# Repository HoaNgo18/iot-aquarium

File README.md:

# IoT Aquarium

Hệ thống theo dõi nhiệt độ, pH và độ đục tương đối của nước trong bể cá. ESP32 gửi dữ liệu qua MQTT về server; giao diện web hiển thị số đo, lịch sử và cảnh báo khi vượt ngưỡng cấu hình.

## Chức năng

- Theo dõi số đo và trạng thái kết nối của thiết bị.
- Xem biểu đồ lịch sử theo từng chỉ số.
- Cấu hình ngưỡng và xác nhận cảnh báo.
- Giả lập dữ liệu để thử hệ thống khi chưa kết nối cảm biến.

## Công nghệ

- **Thiết bị:** ESP32, DS18B20, PH-4502C, cảm biến độ đục MJKDZ.
- **Backend:** Python, FastAPI, PostgreSQL, Mosquitto MQTT.
- **Frontend:** Vue 3, TypeScript, Vite; cập nhật dữ liệu qua WebSocket.
- **Triển khai:** Docker Compose; firmware quản lý bằng PlatformIO.

## Chạy local

Cần Docker Compose. Tạo `.env` từ `.env.example` nếu chưa có, điều chỉnh cấu hình rồi khởi động:

```powershell
if (-not (Test-Path .env)) { Copy-Item .env.example .env }
docker compose up -d --build
```

- Giao diện: http://localhost:5173
- API: http://localhost:8000/docs

## Cấu trúc thư mục

```text
backend/         FastAPI: api -> services/domain -> repositories, migration Alembic
firmware/        ESP32 (PlatformIO), test host, sketch chẩn đoán
frontend/        Dashboard Vue; tests/ là unit test, tests/browser/ là kịch bản Playwright
simulator/       Bộ phát telemetry giả lập qua MQTT
infrastructure/  Cấu hình Mosquitto
scripts/         Smoke test toàn hệ thống; uart/ là công cụ thu và phân tích log Serial
```

## Tài liệu

- [Cấu hình và nạp firmware](firmware/README.md)
- [Chạy dữ liệu giả lập](simulator/README.md)

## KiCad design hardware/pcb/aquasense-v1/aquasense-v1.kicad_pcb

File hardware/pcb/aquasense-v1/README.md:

# AquaSense v1.0 — mạch đế ESP32

Mạch hai lớp **80 × 60 mm**, FR-4 1,6 mm, đồng 1 oz. Cắm ESP32 DevKit 30 chân qua hai header cái 1×15; bốn đầu cảm biến dùng ổ khóa JST-XH để cắm/rút gọn gàng. Không phải mạch ESP32 rời và không thay thế module PH-4502C/MJKDZ.

**Trạng thái:** đã đi dây; KiCad 9.0.2 chạy trong Docker. ERC: 0 lỗi/0 cảnh báo. DRC kèm đối chiếu schematic: 0 vi phạm, 0 kết nối hở, 0 sai khác footprint/net. Chưa sản xuất hay thử điện trên PCB thật.

## Mở và xem

Mở `aquasense-v1.kicad_pro` bằng KiCad 9 trở lên. File sử dụng định dạng KiCad 9, thuộc yêu cầu “KiCad 8 trở lên”. Cần cài bộ thư viện symbol/footprint chuẩn KiCad. Thư viện riêng `aquasense.kicad_sym`, `aquasense.pretty/` được khai báo qua hai bảng thư viện trong project.

- `preview/top-3d.png`, `bottom-3d.png`: ảnh bo trần, chưa lắp linh kiện; máy dựng ảnh không cài gói mô hình 3D linh kiện.
- `preview/pcb-top.svg`: đường đồng và lụa mặt trên.
- `preview/print-1to1.pdf`: mặt trên khổ A4 tỉ lệ 1:1, kèm thước chuẩn 50 mm; khi in phải chọn 100%/Actual size.
- `preview/schematic.pdf`, `schematic.png`, `aquasense-v1.svg`: sơ đồ nguyên lý.
- `reports/erc.rpt`, `drc.rpt`: báo cáo KiCad cuối cùng, không có mục loại trừ lỗi.
- `reports/design-audit.json`: toàn bộ gán net, thứ tự chân JST-XH, ba GPIO, khoảng cách socket và vùng anten đã được kiểm tra.
- `bom.csv`: một hàng cho mỗi reference. U1 tính **1 bộ gồm 2 socket cái 1×15**, không phải hai board ESP32.
- `fab/aquasense-v1-gerber.zip`: Gerber, PTH/NPTH Excellon drill, dùng đặt PCB trần.

## Kích thước socket đã xác nhận

Khoảng cách tâm hai hàng socket **đã đo được 25,4 mm trên board ESP32 thật ngày 18/11/2026**. Board được xác nhận là module ESP-WROOM-32S 30 chân, nhãn chân kiểu DOIT DevKit V1. Giữ `row_spacing_mm = 25.4`. Vẫn nên in `preview/print-1to1.pdf` ở 100% và đặt board thật lên trước khi đặt gia công để đối chiếu vị trí USB, anten và chiều dài module.

Thông số nằm ở `parameters.json`, khóa `row_spacing_mm`. `pitch_mm` = 2,54 mm; 15 chân/hàng. Sau khi đổi tham số, phải chạy lại toàn bộ pipeline để tạo footprint, vị trí pad, đường mạch, keepout, ERC/DRC và Gerber. Không kéo giãn footprint bằng scale.

Nhìn mặt trên, USB hướng xuống: hàng trái từ EN đến VIN; hàng phải từ D23 đến 3V3. Cắm lệch/đảo chiều có thể đưa 5 V vào chân 3,3 V. Hai pad vuông là đầu trên của hai hàng, **không phải vị trí USB**.

| U1 | Chân | Net |
|---|---|---|
| 4, hàng trái thứ 4 | D34 / GPIO34 | PH_ADC |
| 5, hàng trái thứ 5 | D35 / GPIO35 | TURB_ADC |
| 26, hàng phải thứ 11 | D4 / GPIO4 | TEMP_DQ |
| 9, hàng trái thứ 9 | D26 / GPIO26 | LED_OUT, tùy chọn |
| 10, hàng trái thứ 10 | D27 / GPIO27 | PIR_OUT, tùy chọn |
| 14 và 29 | GND | GND chung |
| 15 | VIN | +5V_RAW từ USB |
| 30 | 3V3 | +3V3 từ bộ ổn áp DevKit |

Toàn bộ thứ tự 30 chân nằm trong symbol riêng và `design-manifest.json`; các GPIO không dùng được đánh dấu NC trên sơ đồ, không nối đồng sang chân khác.

## Đầu nối cảm biến

Pin 1 là pad vuông. J1–J4 dùng ổ JST-XH chính hãng bước **2,50 mm**: J1/J3/J4 là `B3B-XH-A`, J2 là `B4B-XH-A`. Tất cả mặt khóa quay về cạnh trái; tên module và từng chân được in ngay cạnh ổ.

| Đầu nối | Pin 1 | Pin 2 | Pin 3 | Pin 4 |
|---|---|---|---|---|
| J1 — DS18B20, XH 3P | VDD, đỏ, 3V3 | GND, đen | DQ, vàng, GPIO4 | — |
| J2 — PH-4502C, XH 4P | PO, qua chia áp | GND | GND | V+, 5V sau F1 |
| J3 — MJKDZ, XH 3P | VCC, 5V sau F1 | OUT, qua chia áp | GND | — |
| J4 — HC-SR501, XH 3P | VCC, 5V sau F1 | OUT, GPIO27 | GND | — |

DS18B20 sử dụng **3 dây cấp nguồn**, không dùng chế độ parasite. R1 = 4,7 kΩ nối DQ lên 3V3. J2 khớp bốn chân cuối `PO G G V+` trong dãy sáu chân `TO DO PO G G V+` của PH-4502C; TO và DO để hở.

### Dây cần mua

- 3 sợi **JST-XH 3P sang Dupont cái 3P**, dài 20–30 cm, cho J1/J3/J4.
- 1 sợi **JST-XH 4P sang Dupont cái 4P**, dài 20–30 cm, cho J2.
- Dây phải đi thẳng `1→1`, `2→2`, `3→3`, và với J2 thêm `4→4`; không dùng dây đảo thứ tự.
- Với đầu dò DS18B20 chưa có đầu XH: hàn hoặc bấm dây đỏ–đen–vàng vào vỏ XH 3P theo đúng `VDD–GND–DQ`, bọc co nhiệt từng mối.

**Cảnh báo:** thứ tự chân trên module thật có thể khác ảnh hoặc lô hàng khác. Trước khi cấp nguồn, phải đối chiếu nhãn in trên module với lụa `PO/G/G/V+`, `VCC/OUT/GND` hoặc `VDD/GND/DQ` trên PCB. Không dựa riêng vào màu dây.

PIR/LED là phần dự phòng, firmware hiện chưa bật. Xác nhận OUT của PIR đúng mức logic 3,3 V trước khi nối.

## Nguồn và chia áp

Nguồn duy nhất là USB của DevKit. U1.VIN nối **+5V_RAW**, qua F1 mới tới **+5V** cấp J2/J3/J4. Không gắn nguồn 5 V ngoài vào cầu đấu; các đầu này là đầu ra nguồn. Đo thực tế VIN và 3V3 của DevKit trước khi cắm cảm biến vì các bản DevKit clone có thể khác đường USB/VIN.

F1 dùng **Bourns MF-RHT050, Ihold 0,5 A**, footprint chuẩn `Fuse_Bourns_MF-RHT050`, chân cách 5,1 mm và lệch 1,2 mm theo thư viện. Không thay bằng MF-RG500: mã đó là loại 5 A. Giá trị hold có derating theo nhiệt độ; xem datasheet Bourns.

- pH: J2.1 (PO) → R2 10 kΩ → PH_ADC → R3 10 kΩ → GND; PH_ADC tới GPIO34 và C3 100 nF xuống GND.
- Độ trong: J3.2 → R4 10 kΩ → TURB_ADC → R5 10 kΩ → GND; TURB_ADC tới GPIO35 và C4 100 nF xuống GND.
- Hai cầu chia áp độc lập. **Không nối PO/OUT trực tiếp vào ESP32.**
- Công thức: V_ADC = V_OUT × 10k/(10k+10k). PO = 5 V → 2,50 V; OUT = 4,5 V → 2,25 V. Hai điện trở 1% lệch bất lợi cho PO 5 V vẫn chỉ khoảng 2,525 V.
- Điện trở đều 1%, 1/4 W. Hằng số RC danh định tại ADC: (10k || 10k) × 100 nF = 0,5 ms.
- C1 100 µF/16 V và C2 100 nF lọc nguồn 5 V; C5 10 µF/16 V và C6 100 nF lọc 3V3. C1/C5 có phân cực, chân + là pad vuông; không đảo.
- LED dự phòng: GPIO26 → R6 330 Ω → anode D1 → cathode GND. Pad 1 D1 là cathode.

| Test point | Đo so với TP3 GND |
|---|---|
| TP1 | +5V sau cầu chì |
| TP2 | +3V3 |
| TP3 | GND |
| TP4 | PH_ADC, điện áp đã chia đôi |
| TP5 | TURB_ADC, điện áp đã chia đôi |
| TP6 | TEMP_DQ |

## Layout và anten

Đường tín hiệu ≥0,3 mm; ba rail nguồn ≥0,7 mm; clearance ≥0,2 mm; via 0,6/0,3 mm. PCB có hai mặt GND và via khâu quanh mép/nhóm analog. Bốn lỗ NPTH 3,2 mm, tâm cách mép 3,5 mm, dành cho vít M3 và trụ đỡ cách điện.

Vùng rule-area **x=32..64 mm, y=5..18 mm** cấm đồng, tracks, vias và pads trên cả F.Cu/B.Cu. Bo bắt đầu tại y=5 mm. Không đặt linh kiện carrier trong vùng anten này; chú thích nằm trên lụa, không phải đồng. DRC kiểm tra keepout; audit cũng dò nội vùng trên hai mặt ở bước 0,25 mm, không phát hiện đồng.

Anten ở đầu trên, USB ở đầu dưới. Outline thân DevKit trên F.Fab là giả định cơ khí, chưa xác nhận kích thước board thật. Bản này giữ một phần substrate không đồng bên dưới anten; **chưa giả định chắc anten nhô hẳn ngoài bo**. Cổng USB được hướng về mép dưới, vị trí thực tế cần kiểm bằng board thật cùng cáp.

C3/C4 nằm gần header ADC; đường analog được đi trước. Nhóm analog ở bên trái U1, tách vùng anten và LED/PIR. J1–J4 xếp thành một dãy ở `x=11,5 mm`, cùng xoay `90°`: J2 tại `y=16,0`, J3 tại `27,5`, J1 tại `38,5`, J4 tại `49,5 mm`. Mặt khóa đều hướng ra cạnh trái và mép trước ổ cách cạnh bo khoảng 8,65 mm, đủ vùng thao tác đầu dây. C1/C2, R2–R5, C5 và TP1/TP4/TP5 được dời sang phải để nhường thân ổ và lụa chân; khối analog vẫn ở gần GPIO34/35.

## Hàn và thử lần đầu

1. Nếu đặt **PCB trần**, vẫn phải hàn điện trở, tụ, PTC, bốn ổ JST-XH và socket ESP32. Muốn nhận về chỉ cắm dây, cần đặt **PCBA có lắp THT** theo `bom.csv`.
2. Khi lắp thủ công, hàn socket ESP32 sau cùng và dùng DevKit chưa cấp điện làm dưỡng để giữ hai hàng song song; không hàn chân DevKit vào carrier.
3. Kiểm tra thông mạch GND, cầu chia áp và kiểm tra không chập +5V/3V3/GND. Đo R2/R3/R4/R5 trước khi cấp nguồn; tụ có thể khiến số đo thay đổi lúc đầu.
4. Cắm ESP32 đúng chiều, cấp USB; đo TP1/TP2. Sau đó ngắt nguồn trước khi cắm lần lượt từng module.
5. Đối chiếu TP4/TP5 với PO/OUT bằng đồng hồ, phải gần tỷ lệ 1/2. Sau đó thử DS18B20 và dữ liệu dashboard.
6. **Đặt lại mốc nước sạch**: PCB cấp module độ trong bằng 5 V, khác cấu hình breadboard 3,3 V trước đó. Không tái dùng mốc 294/1608 mV một cách máy móc. Giữ đầu dò trong nước sạch ổn định, không bọt khí, rồi đặt mốc mới.
7. Kiểm tra/hiệu chuẩn lại pH bằng buffer 4,01 / 6,86 / 9,18 theo nhiệt độ và hướng dẫn pha của gói. Giá trị hiệu chuẩn phải là điện áp GPIO34 sau chia áp. PCB thêm tụ lọc và thay dây nên cần kiểm chứng lại.

Chưa thay firmware, chưa thay dữ liệu hiệu chuẩn và chưa đặt hàng sản xuất.

## Tái tạo thiết kế

Các script bổ sung để dễ kiểm tra, không cần chạy để mở file KiCad:

1. `generate.py`: tham số, symbol riêng, footprint riêng, schematic, BOM và PCB placement.
2. `route.py`: đi dây hai lớp, phủ GND, via khâu.
3. `polish.py`: bố trí lụa tránh pad/mask và chữ khác.
4. `finish_schematic.py`: bố trí nhãn trên sơ đồ.
5. Xuất netlist bằng `kicad-cli sch export netlist ... -o reports/netlist.net`.
6. `verify.py`: đồng bộ tên net Eeschema/PCB và kiểm bảng nối, bề rộng đường, anten.
7. `fabricate.py`: xuất Gerber, drill, ảnh 3D, SVG mặt trên, PDF 1:1, zip và SHA-256.

Chạy toàn bộ từ đầu trong môi trường KiCad bằng một lệnh:

```bash
python3 build.py
```

`build.py` dừng ngay nếu ERC/DRC có vi phạm; không sử dụng lại zip cũ sau khi thay layout.

Môi trường đã dùng: Debian trixie, KiCad 9.0.2, `/usr/bin/python3` với `pcbnew`, `sexpdata`, `cairosvg`. Docker chỉ dùng làm công cụ; không cài KiCad vào Windows. Các footprint chuẩn vẫn trỏ tới thư viện KiCad, không sao chép thư viện chuẩn vào repo.

Nguồn đối chiếu: [KiCad](https://www.kicad.org/), [datasheet MF-RHT](https://www.bourns.com/docs/product-datasheets/mf-rht.pdf). Lựa chọn PCB trần ở JLCPCB: 2 lớp, FR-4, 1,6 mm, 1 oz; kiểm tra preview của nhà sản xuất trước khi thanh toán. BOM đã ghi mã ổ XH nhưng vẫn cần bổ sung mã đặt hàng/nhà sản xuất cho toàn bộ linh kiện nếu dùng dịch vụ PCBA tự động.

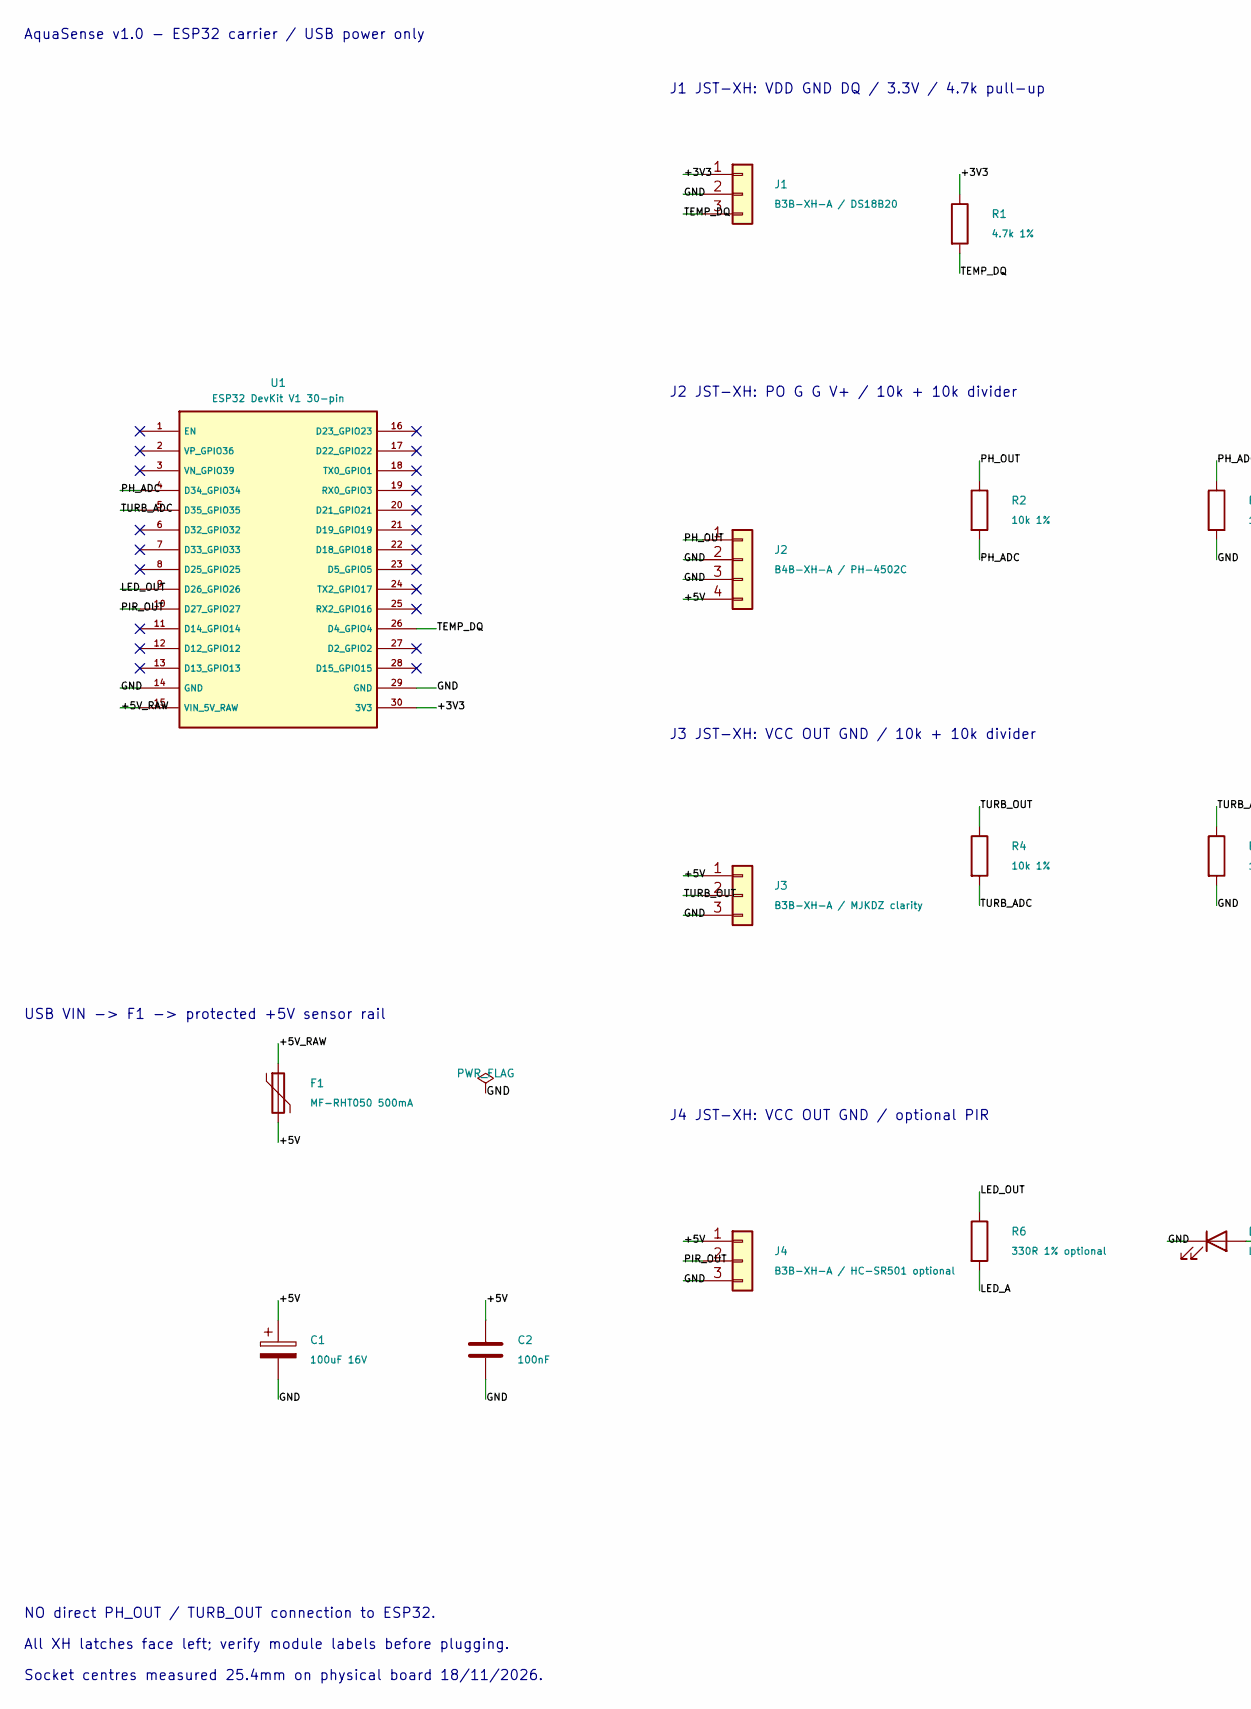
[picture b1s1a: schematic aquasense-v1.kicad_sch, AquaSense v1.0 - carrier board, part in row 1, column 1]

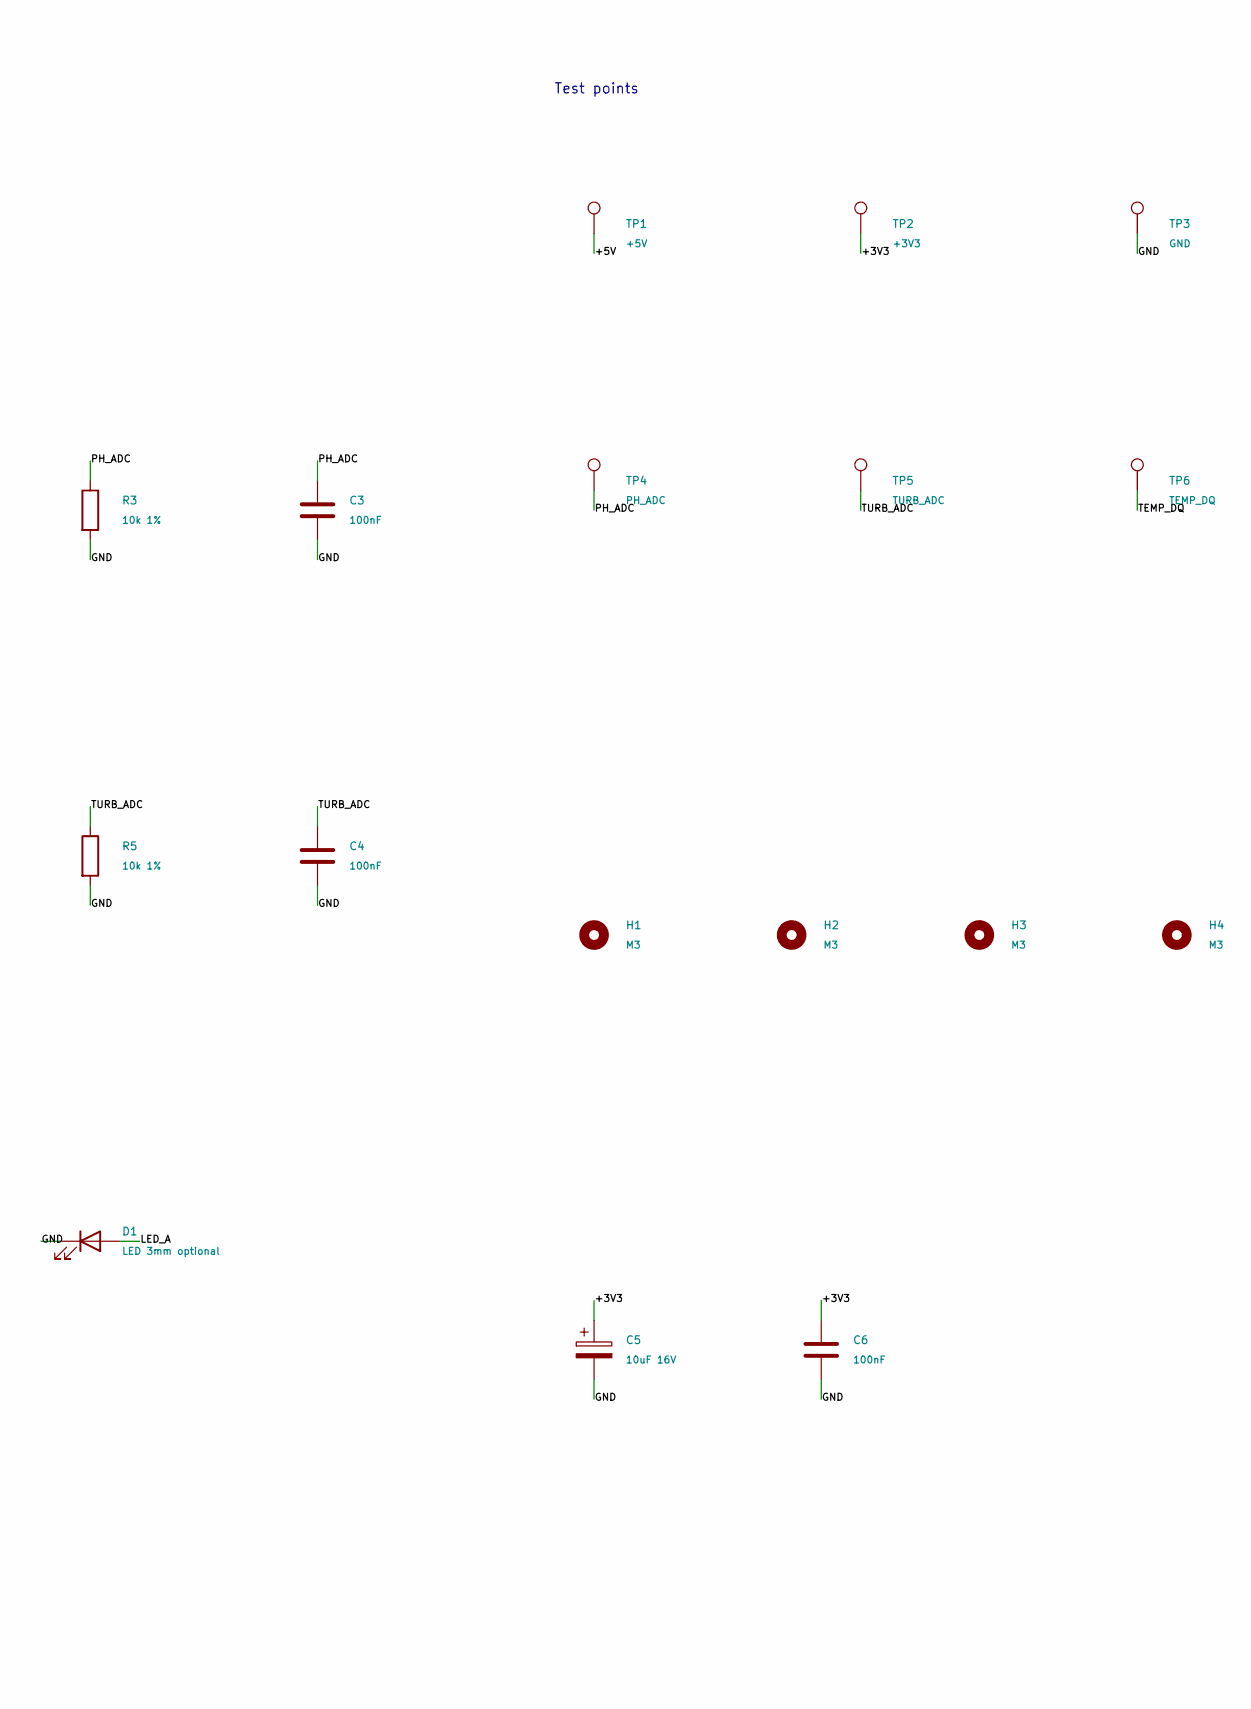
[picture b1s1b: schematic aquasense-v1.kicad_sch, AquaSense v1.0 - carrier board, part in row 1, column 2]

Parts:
C1: 100uF 16V; CP_Radial_D6.3mm_P2.50mm
C2, C3, C4, C6: 100nF; C_Disc_D5.0mm_W2.5mm_P5.00mm
C5: 10uF 16V; CP_Radial_D5.0mm_P2.00mm
D1: LED 3mm optional; LED_D3.0mm
F1: MF-RHT050 500mA; Fuse_Bourns_MF-RHT050
H1, H2, H3, H4: M3; MountingHole_3.2mm_M3
J1: B3B-XH-A / DS18B20; JST_XH_B3B-XH-A_1x03_P2.50mm_Vertical
J2: B4B-XH-A / PH-4502C; JST_XH_B4B-XH-A_1x04_P2.50mm_Vertical
J3: B3B-XH-A / MJKDZ clarity; JST_XH_B3B-XH-A_1x03_P2.50mm_Vertical
J4: B3B-XH-A / HC-SR501 optional; JST_XH_B3B-XH-A_1x03_P2.50mm_Vertical
R1: 4.7k 1%; R_Axial_DIN0207_L6.3mm_D2.5mm_P10.16mm_Horizontal
R2, R3, R4, R5: 10k 1%; R_Axial_DIN0207_L6.3mm_D2.5mm_P10.16mm_Horizontal
R6: 330R 1% optional; R_Axial_DIN0207_L6.3mm_D2.5mm_P10.16mm_Horizontal
TP1: +5V; TestPoint_THTPad_D2.0mm_Drill1.0mm
TP2: +3V3; TestPoint_THTPad_D2.0mm_Drill1.0mm
TP3: GND; TestPoint_THTPad_D2.0mm_Drill1.0mm
TP4: PH_ADC; TestPoint_THTPad_D2.0mm_Drill1.0mm
TP5: TURB_ADC; TestPoint_THTPad_D2.0mm_Drill1.0mm
TP6: TEMP_DQ; TestPoint_THTPad_D2.0mm_Drill1.0mm
U1: ESP32 DevKit V1 30-pin; ESP32_DevKit_30

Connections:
/+3V3: C5.1, C6.1, J1.1, R1.1, TP2.1, U1.30 (3V3)
/+5V: C1.1, C2.1, F1.2, J2.4, J3.1, J4.1, TP1.1
/+5V_RAW: F1.1, U1.15 (VIN_5V_RAW)
/GND: C1.2, C2.2, C3.2, C4.2, C5.2, C6.2, D1.1 (K), J1.2, J2.2, J2.3, J3.3, J4.3, R3.2, R5.2, TP3.1, U1.14 (GND), U1.29 (GND)
/LED_A: D1.2 (A), R6.2
/LED_OUT: R6.1, U1.9 (D26_GPIO26)
/PH_ADC: C3.1, R2.2, R3.1, TP4.1, U1.4 (D34_GPIO34)
/PH_OUT: J2.1, R2.1
/PIR_OUT: J4.2, U1.10 (D27_GPIO27)
/TEMP_DQ: J1.3, R1.2, TP6.1, U1.26 (D4_GPIO4)
/TURB_ADC: C4.1, R4.2, R5.1, TP5.1, U1.5 (D35_GPIO35)
/TURB_OUT: J3.2, R4.1

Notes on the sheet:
AquaSense v1.0 - ESP32 carrier / USB power only
USB VIN -> F1 -> protected +5V sensor rail
J1 JST-XH: VDD GND DQ / 3.3V / 4.7k pull-up
J2 JST-XH: PO G G V+ / 10k + 10k divider
J3 JST-XH: VCC OUT GND / 10k + 10k divider
J4 JST-XH: VCC OUT GND / optional PIR
Test points
NO direct PH_OUT / TURB_OUT connection to ESP32.
All XH latches face left; verify module labels before plugging.
Socket centres measured 25.4mm on physical board 18/11/2026.

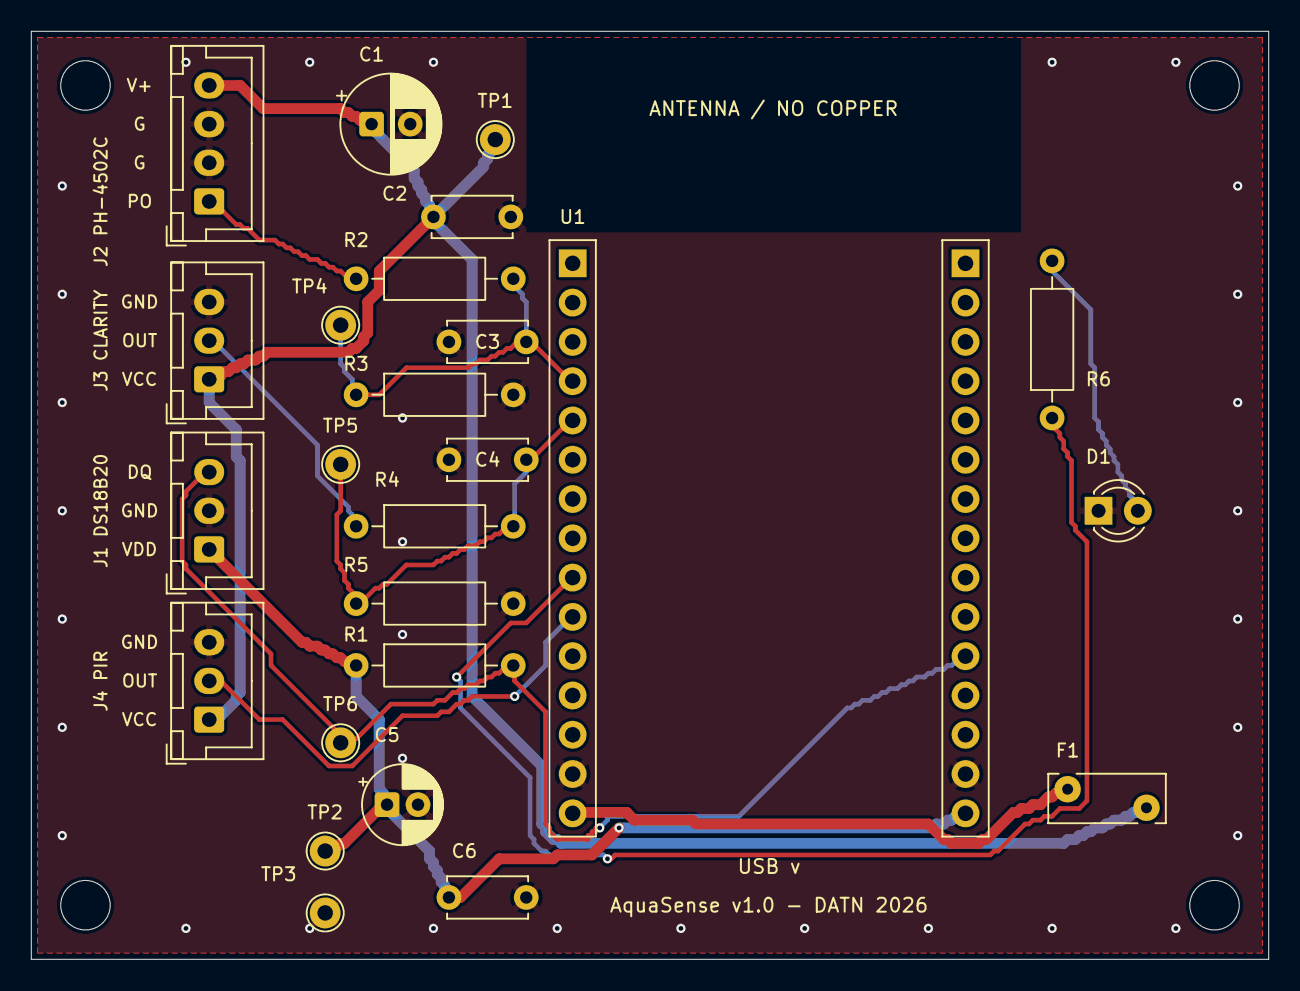
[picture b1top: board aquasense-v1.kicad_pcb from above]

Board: 2 copper layers, 80.0 x 60.0 mm, 29 parts (0 on the bottom side), 12 nets.
